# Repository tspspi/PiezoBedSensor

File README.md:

# Piezo bed leveling sensor interface

NOTE: This readme will be extended soon.

This repository contains the KiCad files for an interface board
between four piezo disk level sensors and an 3D printer. Its based
on an ATMega328P that might either be powered from an existing
5V power rail or via the optional on board power regulator. It allows
interfacing via I2C to perform settings and calibration as well
as an traditional trigger output (for example to interface directly
with an RAMPS board) and an trigger input for a classical inductive
or capacitive leveling sensor.

More information can be found [at my webpage](https://www.tspi.at/2019/09/11/piezobedlevel.html).

Each piezo is biased independently.

## License

See LICENSE.md

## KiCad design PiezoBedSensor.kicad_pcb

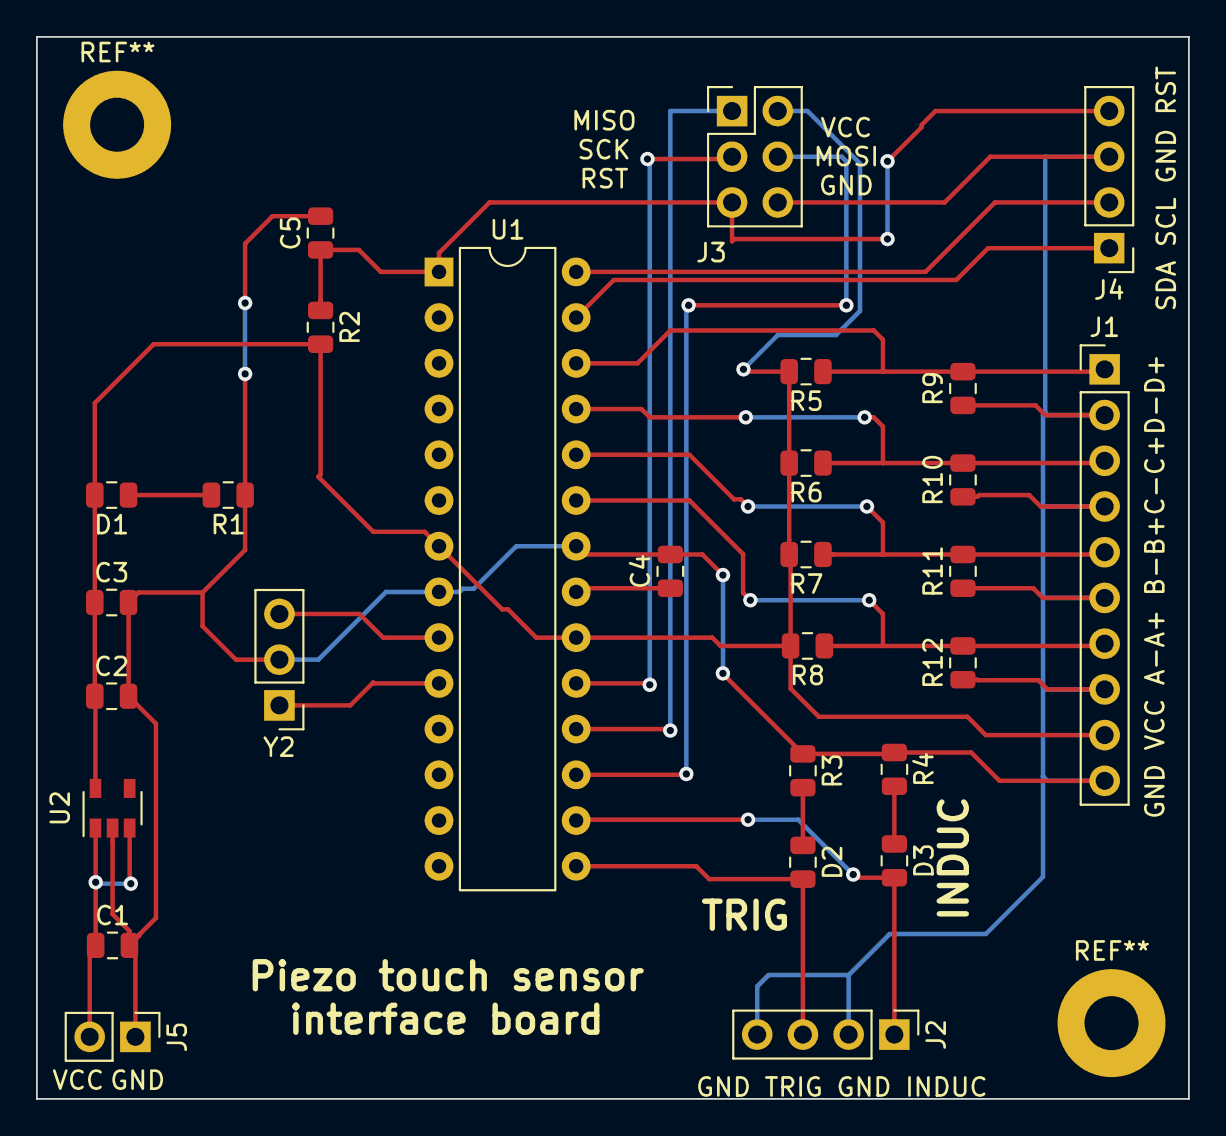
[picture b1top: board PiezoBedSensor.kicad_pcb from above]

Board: 2 copper layers, 64.0 x 59.0 mm, 28 parts (0 on the bottom side), 21 nets.

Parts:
C1, C2: 10uF; C_0805_2012Metric
C3, C4, C5: 0.1uF; C_0805_2012Metric
D1: LED_Small; C_0805_2012Metric
D2: LED Trig; C_0805_2012Metric
D3: LED Induc; C_0805_2012Metric
J1: Piezo; PinHeader_1x10_P2.54mm_Vertical
J2: TRIG; PinHeader_1x04_P2.54mm_Vertical
J3: ISP; PinHeader_2x03_P2.54mm_Vertical
J4: I2C; PinHeader_1x04_P2.54mm_Vertical
J5: PSU; PinHeader_1x02_P2.54mm_Vertical
R1, R2, R3, R4: 10k; R_0805_2012Metric
R5, R6, R7, R8, R9, R10, R11, R12: 1M; R_0805_2012Metric
U1: ATmega328P-PU; DIP-28_W7.62mm
U2: MIC5205-5.0YM5; SOT-23-5
Y2: 16/20MHz; PinHeader_1x03_P2.54mm_Vertical

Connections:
+5V: C2.1, C3.1, D1.2, J1.9, J3.2, R2.2, R5.2, R6.2, R7.2, R8.2, U1.7, U1.20, U2.5
GND: C1.2, C2.2, C3.2, C4.2, C5.2, J1.2, J1.4, J1.6, J1.8, J1.10, J2.2, J2.4, J3.6, J4.3, J5.1, R1.1, R3.1, R4.1, R9.1, R10.1, R11.1, R12.1, U1.8, U1.22, U2.2, Y2.2
unnamed: C1.1, J5.2, U2.1, U2.3
unnamed: C4.1, U1.21
unnamed: C5.1, J3.5, J4.4, R2.1, U1.1
unnamed: D1.1, R1.2
unnamed: D2.1, R3.2
unnamed: D2.2, J2.3, U1.15
unnamed: D3.1, R4.2
unnamed: D3.2, J2.1, U1.16
unnamed: J1.1, R5.1, R9.2, U1.26
unnamed: J1.3, R6.1, R10.2, U1.25
unnamed: J1.5, R7.1, R11.2, U1.24
unnamed: J1.7, R8.1, R12.2, U1.23
unnamed: J3.1, U1.18
unnamed: J3.3, U1.19
unnamed: J3.4, U1.17
unnamed: J4.1, U1.27
unnamed: J4.2, U1.28
unnamed: U1.9, Y2.3
unnamed: U1.10, Y2.1

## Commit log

2019-09-17 Added basic readme
2019-09-17 Extended README and added LICENSE
2019-09-19 Updated README.md with link to project description
